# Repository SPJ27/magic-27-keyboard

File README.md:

# Magic 27

Magic 27 is a aula f75 style keyboard designed completely from scrartch. It uses marbastlib, akko creamy blue switches, and 3d printed case.
I am building this because I wanted to make my own keyboard rather than buying premade ones. From this project, I learned skills such as cad designing, pcb designing, and a lot about mechanical keyboards.

Journal 5: ~3hrs
Completed the project! I designed the case, and also added the 3d models for different keys. Designing the case took a lot of time, and i have only designed the bottom holder for now. In, future, I will make the top cover if needed.

Journal 5: ~1hr 30mins
Routed all of the paths, fixed some errors, and the pcb is ready. I had to reroute twice cause the paths were colliding. Routing had taken a lot of time, because I had to connect each of them individually.

Journal 4: ~1hr 30mins

Added all of diodes - it was extremely time consuming as I had to place them individually. Also, I have started making the basic routes.

Journal 3: ~1hr

So I remade the pcb as it got corrupted the last time. This time it took way less time as compared to the previous version as I already knew things that i should have done earlier - for example i should have named the components by there key for easier positioning and whatnot.

Journal 2: ~3hrs 30mins

I switched from kicad 8.0 to kicad 10, so my original work with pcb is now showing as corrupted when I woke up this morning. I have a few screenshots of prev versions.

Journal 1: ~1hr 50mins

Created the basic pcb - will now rearrange and rename all of the switches, and then arrange all of them in pcb editor.

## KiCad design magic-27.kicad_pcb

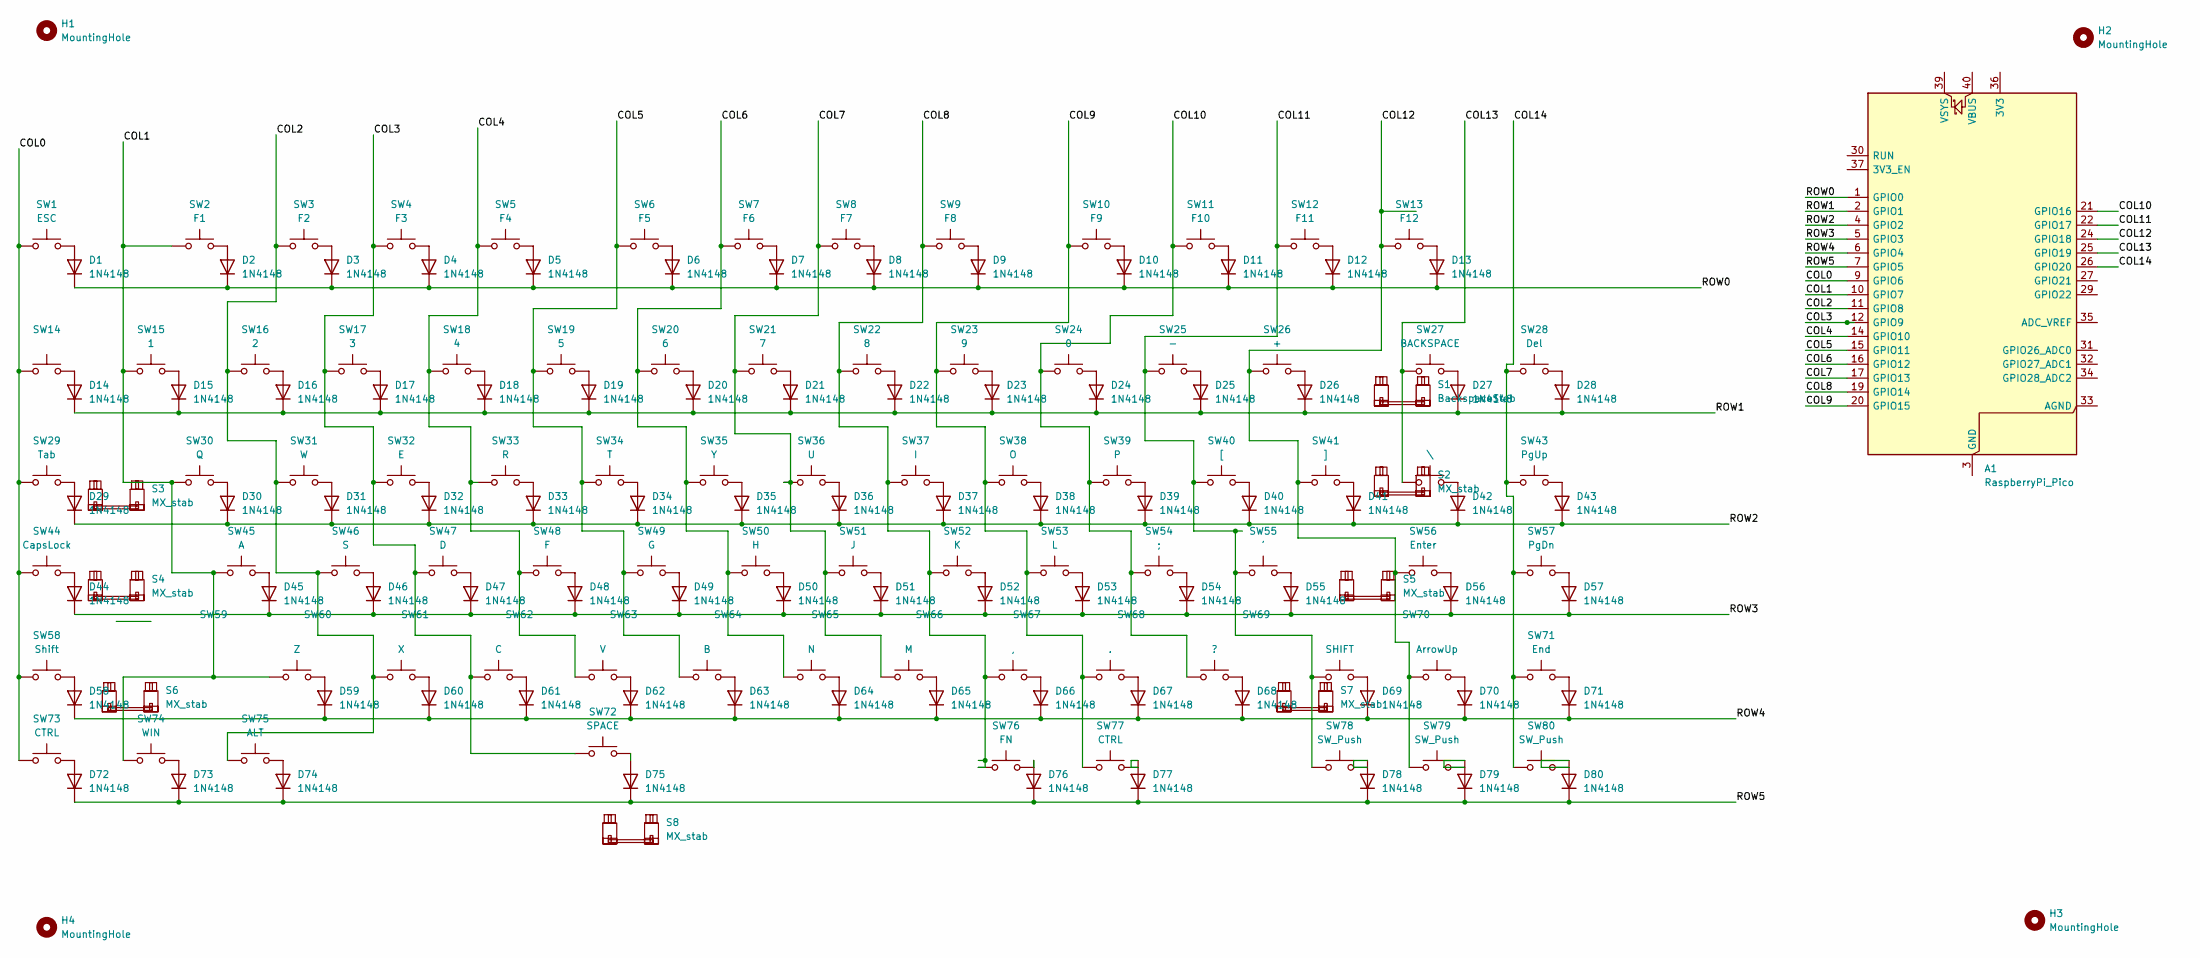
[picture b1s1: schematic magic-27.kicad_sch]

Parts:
A1: RaspberryPi_Pico; RaspberryPi_Pico_Common_THT
D1, D2, D3, D4, D5, D6, D7, D8, D9, D10, D11, D12, D13, D14, D15, D16, D17, D18, D19, D20, D21, D22, D23, D24, D25, D26, D27, D28, D29, D30, D31, D32, D33, D34, D35, D36, D37, D38, D39, D40, D41, D42, D43, D44, D45, D46, D47, D48, D49, D50, D51, D52, D53, D54, D55, D56, D57, D58, D59, D60, D61, D62, D63, D64, D65, D66, D67, D68, D69, D70, D71, D72, D73, D74, D75, D76, D77, D78, D79, D80: 1N4148; D_DO-35_SOD27_P7.62mm_Horizontal
H1, H2, H3, H4: MountingHole; ToolingHole_1.152mm
S1: BackspaceStab; STAB_MX_2u
S2, S6, S7: MX_stab; STAB_MX_2u
S3, S4: MX_stab; STAB_MX_2.25u
S5: MX_stab; STAB_MX_2.75u
S8: MX_stab; STAB_MX_6u
SW1: ESC; SW_MX_1u
SW2: F1; SW_MX_1u
SW3: F2; SW_MX_1u
SW4: F3; SW_MX_1u
SW5: F4; SW_MX_1u
SW6: F5; SW_MX_1u
SW7: F6; SW_MX_1u
SW8: F7; SW_MX_1u
SW9: F8; SW_MX_1u
SW10: F9; SW_MX_1u
SW11: F10; SW_MX_1u
SW12: F11; SW_MX_1u
SW13: F12; SW_MX_1u
SW14: SW_MX_1u
SW15: 1; SW_MX_1u
SW16: 2; SW_MX_1u
SW17: 3; SW_MX_1u
SW18: 4; SW_MX_1u
SW19: 5; SW_MX_1u
SW20: 6; SW_MX_1u
SW21: 7; SW_MX_1u
SW22: 8; SW_MX_1u
SW23: 9; SW_MX_1u
SW24: 0; SW_MX_1u
SW25: -; SW_MX_1u
SW26: +; SW_MX_1u
SW27: BACKSPACE; SW_MX_1u
SW28: Del; SW_MX_1u
SW29: Tab; SW_MX_1.5u
SW30: Q; SW_MX_1u
SW31: W; SW_MX_1u
SW32: E; SW_MX_1u
SW33: R; SW_MX_1u
SW34: T; SW_MX_1u
SW35: Y; SW_MX_1u
SW36: U; SW_MX_1u
SW37: I; SW_MX_1u
SW38: O; SW_MX_1u
SW39: P; SW_MX_1u
SW40: [; SW_MX_1u
SW41: ]; SW_MX_1u
SW42: \; SW_MX_1.5u
SW43: PgUp; SW_MX_1u
SW44: CapsLock; SW_MX_1.75u
SW45: A; SW_MX_1u
SW46: S; SW_MX_1u
SW47: D; SW_MX_1u
SW48: F; SW_MX_1u
SW49: G; SW_MX_1u
SW50: H; SW_MX_1u
SW51: J; SW_MX_1u
SW52: K; SW_MX_1u
SW53: L; SW_MX_1u
SW54: ;; SW_MX_1u
SW55: '; SW_MX_1u
SW56: Enter; SW_MX_1u
SW57: PgDn; SW_MX_1u
SW58: Shift; SW_MX_1u
SW59: Z; SW_MX_1u
SW60: X; SW_MX_1u
SW61: C; SW_MX_1u
SW62: V; SW_MX_1u
SW63: B; SW_MX_1u
SW64: N; SW_MX_1u
SW65: M; SW_MX_1u
SW66: ,; SW_MX_1u
SW67: .; SW_MX_1u
SW68: ?; SW_MX_1u
SW69: SHIFT; SW_MX_1u
SW70: ArrowUp; SW_MX_1u
SW71: End; SW_MX_1u
SW72: SPACE; SW_MX_1u
SW73, SW77: CTRL; SW_MX_1.25u
SW74: WIN; SW_MX_1.25u
SW75: ALT; SW_MX_1.25u
SW76: FN; SW_MX_1.25u
SW78, SW79, SW80: SW_Push; SW_MX_1u

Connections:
/COL0: A1.9 (GPIO6), SW1.1, SW14.1, SW29.1, SW44.1, SW58.1, SW73.1
/COL1: A1.10 (GPIO7), SW2.1, SW15.1, SW30.1, SW45.1, SW59.1, SW74.1
/COL2: A1.11 (GPIO8), SW3.1, SW16.1, SW31.1, SW46.1, SW60.1, SW75.1
/COL3: A1.12 (GPIO9), SW4.1, SW17.1, SW32.1, SW47.1, SW61.1, SW72.1
/COL4: A1.14 (GPIO10), SW5.1, SW18.1, SW33.1, SW48.1, SW62.1
/COL5: A1.15 (GPIO11), SW6.1, SW19.1, SW34.1, SW49.1, SW63.1
/COL6: A1.16 (GPIO12), SW7.1, SW20.1, SW35.1, SW50.1, SW64.1
/COL7: A1.17 (GPIO13), SW8.1, SW21.1, SW36.1, SW51.1, SW65.1
/COL8: A1.19 (GPIO14), SW9.1, SW22.1, SW37.1, SW52.1, SW66.1, SW76.1
/COL9: A1.20 (GPIO15), SW10.1, SW23.1, SW38.1, SW53.1, SW67.1, SW77.1
/COL10: A1.21 (GPIO16), SW11.1, SW24.1, SW39.1, SW54.1, SW68.1
/COL11: A1.22 (GPIO17), SW12.1, SW25.1, SW40.1, SW55.1, SW69.1, SW78.1
/COL12: A1.24 (GPIO18), SW13.1, SW26.1, SW41.1, SW56.1, SW70.1, SW79.1
/COL13: A1.25 (GPIO19), SW27.1, SW42.1
/COL14: A1.26 (GPIO20), SW28.1, SW43.1, SW57.1, SW71.1, SW80.1
/ROW0: A1.1 (GPIO0), D1.1 (K), D2.1 (K), D3.1 (K), D4.1 (K), D5.1 (K), D6.1 (K), D7.1 (K), D8.1 (K), D9.1 (K), D10.1 (K), D11.1 (K), D12.1 (K), D13.1 (K)
/ROW1: A1.2 (GPIO1), D14.1 (K), D15.1 (K), D16.1 (K), D17.1 (K), D18.1 (K), D19.1 (K), D20.1 (K), D21.1 (K), D22.1 (K), D23.1 (K), D24.1 (K), D25.1 (K), D26.1 (K), D27.1 (K), D28.1 (K)
/ROW2: A1.4 (GPIO2), D29.1 (K), D30.1 (K), D31.1 (K), D32.1 (K), D33.1 (K), D34.1 (K), D35.1 (K), D36.1 (K), D37.1 (K), D38.1 (K), D39.1 (K), D40.1 (K), D41.1 (K), D42.1 (K), D43.1 (K)
/ROW3: A1.5 (GPIO3), D44.1 (K), D45.1 (K), D46.1 (K), D47.1 (K), D48.1 (K), D49.1 (K), D50.1 (K), D51.1 (K), D52.1 (K), D53.1 (K), D54.1 (K), D55.1 (K), D56.1 (K), D57.1 (K)
/ROW4: A1.6 (GPIO4), D58.1 (K), D59.1 (K), D60.1 (K), D61.1 (K), D62.1 (K), D63.1 (K), D64.1 (K), D65.1 (K), D66.1 (K), D67.1 (K), D68.1 (K), D69.1 (K), D70.1 (K), D71.1 (K)
/ROW5: A1.7 (GPIO5), D72.1 (K), D73.1 (K), D74.1 (K), D75.1 (K), D76.1 (K), D77.1 (K), D78.1 (K), D79.1 (K), D80.1 (K)
unnamed: A1.3 (GND), A1.8 (GND), A1.13 (GND), A1.18 (GND), A1.23 (GND), A1.28 (GND), A1.38 (GND)
unnamed: D1.2 (A), SW1.2
unnamed: D2.2 (A), SW2.2
unnamed: D3.2 (A), SW3.2
unnamed: D4.2 (A), SW4.2
unnamed: D5.2 (A), SW5.2
unnamed: D6.2 (A), SW6.2
unnamed: D7.2 (A), SW7.2
unnamed: D8.2 (A), SW8.2
unnamed: D9.2 (A), SW9.2
unnamed: D10.2 (A), SW10.2
unnamed: D11.2 (A), SW11.2
unnamed: D12.2 (A), SW12.2
unnamed: D13.2 (A), SW13.2
unnamed: D14.2 (A), SW14.2
unnamed: D15.2 (A), SW15.2
unnamed: D16.2 (A), SW16.2
unnamed: D17.2 (A), SW17.2
unnamed: D18.2 (A), SW18.2
unnamed: D19.2 (A), SW19.2
unnamed: D20.2 (A), SW20.2
unnamed: D21.2 (A), SW21.2
unnamed: D22.2 (A), SW22.2
unnamed: D23.2 (A), SW23.2
unnamed: D24.2 (A), SW24.2
unnamed: D25.2 (A), SW25.2
unnamed: D26.2 (A), SW26.2
unnamed: D27.2 (A), SW27.2
unnamed: D28.2 (A), SW28.2
unnamed: D29.2 (A), SW29.2
unnamed: D30.2 (A), SW30.2
unnamed: D31.2 (A), SW31.2
unnamed: D32.2 (A), SW32.2
unnamed: D33.2 (A), SW33.2
unnamed: D34.2 (A), SW34.2
unnamed: D35.2 (A), SW35.2
unnamed: D36.2 (A), SW36.2
unnamed: D37.2 (A), SW37.2
unnamed: D38.2 (A), SW38.2
unnamed: D39.2 (A), SW39.2
unnamed: D40.2 (A), SW40.2
unnamed: D41.2 (A), SW41.2
unnamed: D42.2 (A), SW42.2
unnamed: D43.2 (A), SW43.2
unnamed: D44.2 (A), SW44.2
unnamed: D45.2 (A), SW45.2
unnamed: D46.2 (A), SW46.2
unnamed: D47.2 (A), SW47.2
unnamed: D48.2 (A), SW48.2
unnamed: D49.2 (A), SW49.2
unnamed: D50.2 (A), SW50.2
unnamed: D51.2 (A), SW51.2
unnamed: D52.2 (A), SW52.2
unnamed: D53.2 (A), SW53.2
unnamed: D54.2 (A), SW54.2
unnamed: D55.2 (A), SW55.2
unnamed: D56.2 (A), SW56.2
unnamed: D57.2 (A), SW57.2
unnamed: D58.2 (A), SW58.2
unnamed: D59.2 (A), SW59.2
unnamed: D60.2 (A), SW60.2
unnamed: D61.2 (A), SW61.2
unnamed: D62.2 (A), SW62.2
unnamed: D63.2 (A), SW63.2
unnamed: D64.2 (A), SW64.2
unnamed: D65.2 (A), SW65.2
unnamed: D66.2 (A), SW66.2
unnamed: D67.2 (A), SW67.2
unnamed: D68.2 (A), SW68.2
unnamed: D69.2 (A), SW69.2
unnamed: D70.2 (A), SW70.2
unnamed: D71.2 (A), SW71.2
unnamed: D72.2 (A), SW73.2
unnamed: D73.2 (A), SW74.2
unnamed: D74.2 (A), SW75.2
unnamed: D75.2 (A), SW72.2
unnamed: D76.2 (A), SW76.2
unnamed: D77.2 (A), SW77.2
unnamed: D78.2 (A), SW78.2
unnamed: D79.2 (A), SW79.2
unnamed: D80.2 (A), SW80.2

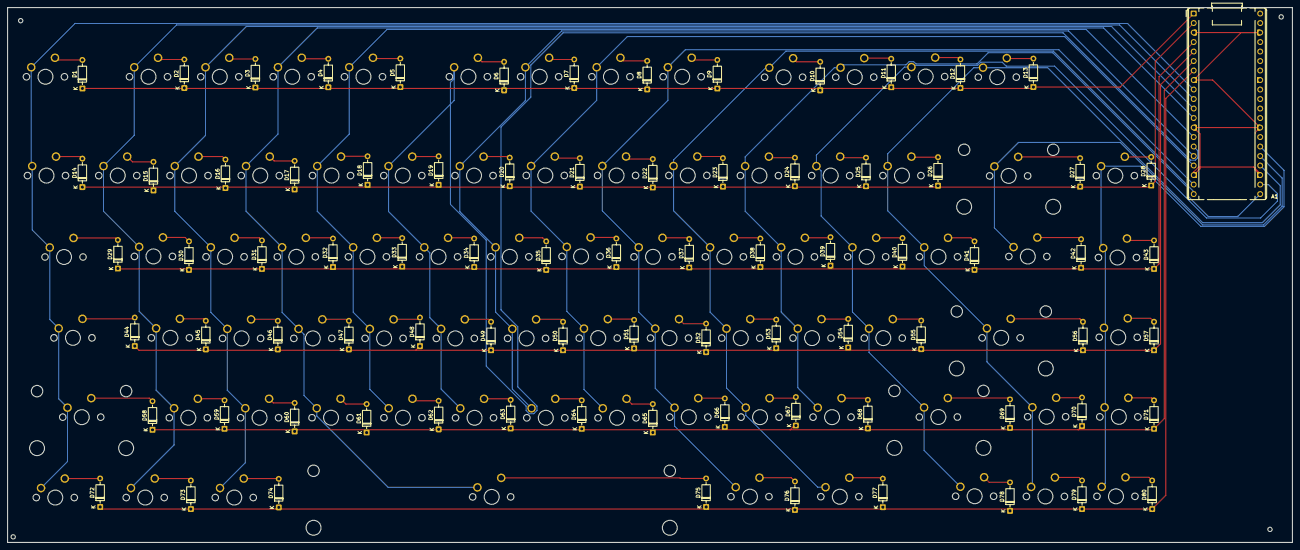
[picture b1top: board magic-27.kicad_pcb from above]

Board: 2 copper layers, 343.5 x 143.0 mm, 170 parts (0 on the bottom side), 102 nets.
